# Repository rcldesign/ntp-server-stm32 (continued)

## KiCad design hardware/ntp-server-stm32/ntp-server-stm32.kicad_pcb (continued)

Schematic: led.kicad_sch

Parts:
C168: 10uF; C_1206_3216Metric; TOLERANCE 10%; VOLTAGE 16V; MANUFACTURER_PART_NUMBER CL31B106KOHVPNE; DIGIKEY_PART_NUMBER 1276-6797-1-ND
C169, C185: 0.1uF; C_0402_1005Metric; TOLERANCE 10%; VOLTAGE 16V; MANUFACTURER_PART_NUMBER GCM155R71C104KA55D; DIGIKEY_PART_NUMBER 490-4759-1-ND
C200: 1nF; C_0402_1005Metric; TOLERANCE 5%; VOLTAGE 50V; MANUFACTURER_PART_NUMBER C0402C102J5GECAUTO; DIGIKEY_PART_NUMBER 399-C0402C102J5GECAUTOCT-ND
D5: IN-P55TATRGB; LED_IN-P55TATRGB; MANUFACTURER_PART_NUMBER IN-P55TATRGB; DIGIKEY_PART_NUMBER 1830-1098-1-ND
FB12: 600; 1206; MANUFACTURER_PART_NUMBER BLM31PG601SN1L; DIGIKEY_PART_NUMBER 490-16533-1-ND
Q8, Q9, Q10, Q23: BC847W; SOT-323_SC-70; MANUFACTURER_PART_NUMBER BC847W,135; DIGIKEY_PART_NUMBER 1727-BC847W,135CT-ND
Q22: NSS40300MZ4T1G; SOT-223; MANUFACTURER_PART_NUMBER NSS40300MZ4T1G; DIGIKEY_PART_NUMBER NSS40300MZ4T1GOSCT-ND
R55: 1k; R_0402_1005Metric; TOLERANCE 1%; MANUFACTURER_PART_NUMBER ERJ-2RKF1001X; DIGIKEY_PART_NUMBER P1.00KLCT-ND
R56, R58, R63, R198, R201, R235: 10k; R_0402_1005Metric; TOLERANCE 1%; MANUFACTURER_PART_NUMBER ERJ-2RKF1002X; DIGIKEY_PART_NUMBER P10.0KLCT-ND
R57: 1.5k; R_0402_1005Metric; TOLERANCE 1%; MANUFACTURER_PART_NUMBER ERJ-2RKF1501X; DIGIKEY_PART_NUMBER P1.50KLCT-ND
R59: 60.4; R_0402_1005Metric; TOLERANCE 1%; MANUFACTURER_PART_NUMBER RK73H1ETTP60R4F; DIGIKEY_PART_NUMBER 2019-RK73H1ETTP60R4FCT-ND
R60: 174; R_0402_1005Metric; TOLERANCE 1%; MANUFACTURER_PART_NUMBER ERJ-2RKF1740X; DIGIKEY_PART_NUMBER P174LCT-ND
R61: 221; R_0402_1005Metric; TOLERANCE 1%; MANUFACTURER_PART_NUMBER RK73H1ETTP2210F; DIGIKEY_PART_NUMBER 2019-RK73H1ETTP2210FCT-ND
R62: 3.01k; R_0402_1005Metric; TOLERANCE 1%; MANUFACTURER_PART_NUMBER RK73H1ETTP3011F; DIGIKEY_PART_NUMBER 2019-RK73H1ETTP3011FCT-ND
R199: 150m; R_1206_3216Metric; TOLERANCE 0.5%; MANUFACTURER_PART_NUMBER WSL1206R1500FEA; DIGIKEY_PART_NUMBER WSLC-.15CT-ND
R216: 4.7k; R_0805_2012Metric; TOLERANCE 1%; MANUFACTURER_PART_NUMBER ERJ-6ENF4701V; DIGIKEY_PART_NUMBER P4.70KCCT-ND
R217: 820; R_0805_2012Metric; TOLERANCE 1%; MANUFACTURER_PART_NUMBER ERJ-6ENF8200V; DIGIKEY_PART_NUMBER P820CCT-ND
R234: 4.7k; R_0402_1005Metric; TOLERANCE 1%; MANUFACTURER_PART_NUMBER ERJ-2RKF4701X; DIGIKEY_PART_NUMBER P4.70KLCT-ND
R247, R248, R249, R250, R251, R252: 91; R_0805_2012Metric; TOLERANCE 1%; MANUFACTURER_PART_NUMBER ERJ-6ENF91R0V; DIGIKEY_PART_NUMBER P91.0CCT-ND
R253: 150; R_0805_2012Metric; TOLERANCE 1%; MANUFACTURER_PART_NUMBER ERJ-6ENF1500V; DIGIKEY_PART_NUMBER P150CCT-ND
U54: INA228AQDGSRQ1; VSSOP10_DGS_TEX; MANUFACTURER_PART_NUMBER INA228AQDGSRQ1; DIGIKEY_PART_NUMBER 296-INA228AQDGSRQ1CT-ND
U55: RT9742VGJ5; TSOT-23-5; MANUFACTURER_PART_NUMBER RT9742VGJ5; DIGIKEY_PART_NUMBER 1028-RT9742VGJ5TR-ND

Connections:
3V3: C169.1, U54.6 (VS); also elsewhere on the board
3V3_STM: R201.1; also elsewhere on the board
5V: R59.1, R60.1, R61.1, U55.5 (IN); also elsewhere on the board
GND: C168.2, C169.2, C185.2, C200.2, Q8.2 (E), Q9.2 (E), Q10.2 (E), Q23.2 (E), R56.2, R58.2, R63.2, R198.2, R235.2, R247.2, R248.2, R249.2, R250.2, R251.2, R252.2, R253.2, U54.2 (A0), U54.7 (GND), U55.2 (GND); also elsewhere on the board
I2C_SCL: U54.1 (A1), U54.5 (SCL); also elsewhere on the board
I2C_SDA: U54.4 (SDA); also elsewhere on the board
INA_ALERT_5V_PANEL: U54.3 (ALERT); also elsewhere on the board
LED_B: R55.2; also elsewhere on the board
LED_G: R62.2; also elsewhere on the board
LED_R: R57.2; also elsewhere on the board
unnamed: D5.6 (AB), R59.2
unnamed: D5.4 (AG), R61.2
unnamed: D5.5 (AR), R60.2
unnamed: D5.1 (KB), Q8.3 (C)
unnamed: D5.3 (KG), Q10.3 (C)
unnamed: D5.2 (KR), Q9.3 (C)
unnamed: Q8.1 (B), R55.1, R56.1
unnamed: Q9.1 (B), R57.1, R58.1
unnamed: Q10.1 (B), R62.1, R63.1
unnamed: Q22.1 (B), R217.2, R234.2
unnamed: Q23.1 (B), R216.2, R235.1
unnamed: Q23.3 (C), R217.1
unnamed: C168.1, R199.1, U54.10 (IN+), U55.1 (OUT)
unnamed: FB12.2, R199.2, U54.8 (VBUS), U54.9 (IN-)
PANEL_LEDS_P: Q22.2 (C); also elsewhere on the board
PANEL_LED_EN: R198.1, U55.4 (EN); also elsewhere on the board
PANEL_LED_FAULT: R201.2, U55.3 (nFLG); also elsewhere on the board
PANEL_LED_PWM: R216.1; also elsewhere on the board
PANEL_LED_RED_N_1: R253.1; also elsewhere on the board
PANEL_LED_WHITE_N_1: R247.1; also elsewhere on the board
PANEL_LED_WHITE_N_2: R248.1; also elsewhere on the board
PANEL_LED_WHITE_N_3: R249.1; also elsewhere on the board
PANEL_LED_WHITE_N_4: R250.1; also elsewhere on the board
PANEL_LED_WHITE_N_5: R251.1; also elsewhere on the board
PANEL_LED_WHITE_N_6: R252.1; also elsewhere on the board
V_PANEL_LED: C185.1, C200.1, FB12.1, Q22.3 (E), R234.1

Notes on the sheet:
I2C Address: 0x4C

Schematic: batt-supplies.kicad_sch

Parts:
C88, C89: 10uF; C_1206_3216Metric; TOLERANCE 10%; VOLTAGE 16V; MANUFACTURER_PART_NUMBER CL31B106KOHVPNE; DIGIKEY_PART_NUMBER 1276-6797-1-ND
C90, C91: 3F; DSF305Q3R0; TOLERANCE 5%; VOLTAGE 3V; MANUFACTURER_PART_NUMBER DSF305Q3R0; DIGIKEY_PART_NUMBER 338-DSF305Q3R0-ND
C92, C93, C94, C95, C96, C97: 22uF; C_0805_2012Metric; TOLERANCE 10%; VOLTAGE 16V; MANUFACTURER_PART_NUMBER GRT21BR61C226ME13K; DIGIKEY_PART_NUMBER 490-GRT21BR61C226ME13KCT-ND
C189: 0.1uF; C_0402_1005Metric; TOLERANCE 10%; VOLTAGE 16V; MANUFACTURER_PART_NUMBER GCM155R71C104KA55D; DIGIKEY_PART_NUMBER 490-4759-1-ND
C190, C192: 10nF; C_0402_1005Metric; TOLERANCE 10%; VOLTAGE 50V; MANUFACTURER_PART_NUMBER GCM155R71H103KA55D; DIGIKEY_PART_NUMBER 490-4762-1-ND
C191: 1uF; C_0603_1608Metric; TOLERANCE 10%; VOLTAGE 16V; MANUFACTURER_PART_NUMBER C0603C105K4RACAUTO; DIGIKEY_PART_NUMBER 399-17704-1-ND
FB11: 600; 1206; MANUFACTURER_PART_NUMBER BLM31PG601SN1L; DIGIKEY_PART_NUMBER 490-16533-1-ND
L4, L5: 2.2uH; DR73-2R2-R; MANUFACTURER_PART_NUMBER DR73-2R2-R; DIGIKEY_PART_NUMBER 283-DR73-2R2-RTR-ND
R108, R109, R110, R111, R237, R244: 100k; R_0402_1005Metric; TOLERANCE 1%; MANUFACTURER_PART_NUMBER ERJ-2RKF1003X; DIGIKEY_PART_NUMBER P100KLCT-ND
R112, R113: 13.0k; R_0402_1005Metric; TOLERANCE 1%; MANUFACTURER_PART_NUMBER ERJ-2RKF1302X; DIGIKEY_PART_NUMBER P13.0KLCT-ND
R114, R115: 9.53k; R_0402_1005Metric; TOLERANCE 1%; MANUFACTURER_PART_NUMBER ERJ-2RKF9531X; DIGIKEY_PART_NUMBER P9.53KLCT-ND
R116, R117: 3.09k; R_0402_1005Metric; TOLERANCE 1%; MANUFACTURER_PART_NUMBER ERJ-2RKF3091X; DIGIKEY_PART_NUMBER P3.09KLCT-ND
R238, R245: 2M; R_0402_1005Metric; TOLERANCE 1%; MANUFACTURER_PART_NUMBER ERJ-U02F2004X; DIGIKEY_PART_NUMBER 10-ERJ-U02F2004XCT-ND
R239, R242: 110k; R_0402_1005Metric; TOLERANCE 1%; MANUFACTURER_PART_NUMBER ERJ-2RKF1103X; DIGIKEY_PART_NUMBER P110KLCT-ND
R240, R243: 150k; R_0402_1005Metric; TOLERANCE 1%; MANUFACTURER_PART_NUMBER ERJ-2RKF1503X; DIGIKEY_PART_NUMBER P150KLCT-ND
R241, R246: 10k; R_0402_1005Metric; TOLERANCE 1%; MANUFACTURER_PART_NUMBER ERJ-2RKF1002X; DIGIKEY_PART_NUMBER P10.0KLCT-ND
U34, U35: TPS61094DSSR; SON50P300X200X80-13N; MANUFACTURER_PART_NUMBER TPS61094DSSR; DIGIKEY_PART_NUMBER 296-TPS61094DSSRCT-ND
U67: LMV393; MANUFACTURER_PART_NUMBER LMV393IDGKR; DIGIKEY_PART_NUMBER 296-13993-1-ND

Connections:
3V3: C88.1, C89.1, U34.4 (VIN), U35.4 (VIN); also elsewhere on the board
3V3_STM: R239.1, R241.1, R242.1, R246.1; also elsewhere on the board
5V: FB11.2; also elsewhere on the board
BKP_GPS_PG: R238.2, R241.2, U67.1; also elsewhere on the board
BKP_STM_PG: R245.2, R246.2, U67.7; also elsewhere on the board
GND: C88.2, C89.2, C90.2, C91.2, C92.2, C93.2, C94.2, C95.2, C96.2, C97.2, C189.2, C190.2, C191.2, C192.2, R112.2, R113.2, R114.2, R115.2, R116.2, R117.2, R240.2, R243.2, U34.7 (PGND), U34.8 (AGND), U34.13 (EXP), U35.7 (PGND), U35.8 (AGND), U35.13 (EXP), U67.4 (V-); also elsewhere on the board
GPS_VBAT: C92.1, C94.1, C96.1, R108.1, R110.1, U34.9 (VOUT), U34.10 (VOUT__1); also elsewhere on the board
unnamed: R108.2, U34.3 (EN)
unnamed: R114.1, U34.11 (ICHG)
unnamed: R110.2, U34.2 (MODE)
unnamed: R116.1, U34.1 (OSEL)
unnamed: C90.1, L4.2, R237.1, U34.6 (SUP)
unnamed: L4.1, U34.5 (SW)
unnamed: R112.1, U34.12 (VCHG)
unnamed: R109.2, U35.3 (EN)
unnamed: R115.1, U35.11 (ICHG)
unnamed: R111.2, U35.2 (MODE)
unnamed: R117.1, U35.1 (OSEL)
unnamed: C91.1, L5.2, R244.1, U35.6 (SUP)
unnamed: L5.1, U35.5 (SW)
unnamed: R113.1, U35.12 (VCHG)
unnamed: C190.1, R237.2, R238.1, U67.3 (+)
unnamed: R239.2, R240.1, U67.2 (-)
unnamed: C192.1, R244.2, R245.1, U67.5 (+)
unnamed: R242.2, R243.1, U67.6 (-)
unnamed: C189.1, C191.1, FB11.1, U67.8 (V+)
STM_VBAT: C93.1, C95.1, C97.1, R109.1, R111.1, U35.9 (VOUT), U35.10 (VOUT__1); also elsewhere on the board

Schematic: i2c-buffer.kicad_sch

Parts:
C170: 0.1uF; C_0402_1005Metric; TOLERANCE 10%; VOLTAGE 16V; MANUFACTURER_PART_NUMBER GCM155R71C104KA55D; DIGIKEY_PART_NUMBER 490-4759-1-ND
R202, R203: 4.7k; R_0402_1005Metric; TOLERANCE 1%; MANUFACTURER_PART_NUMBER ERJ-2RKF4701X; DIGIKEY_PART_NUMBER P4.70KLCT-ND
U56: LTC4311ISC6-TRPBF; SOT-6_SC_LIT; MANUFACTURER_PART_NUMBER LTC4311ISC6#TRPBF; DIGIKEY_PART_NUMBER LTC4311ISC6#TRPBFCT-ND

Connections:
3V3_STM: C170.1, R202.1, R203.1, U56.1 (VCC), U56.3 (ENABLE); also elsewhere on the board
GND: C170.2, U56.2 (GND), U56.5 (GND); also elsewhere on the board
I2C_SCL: R202.2, U56.6 (BUS1); also elsewhere on the board
I2C_SDA: R203.2, U56.4 (BUS2); also elsewhere on the board

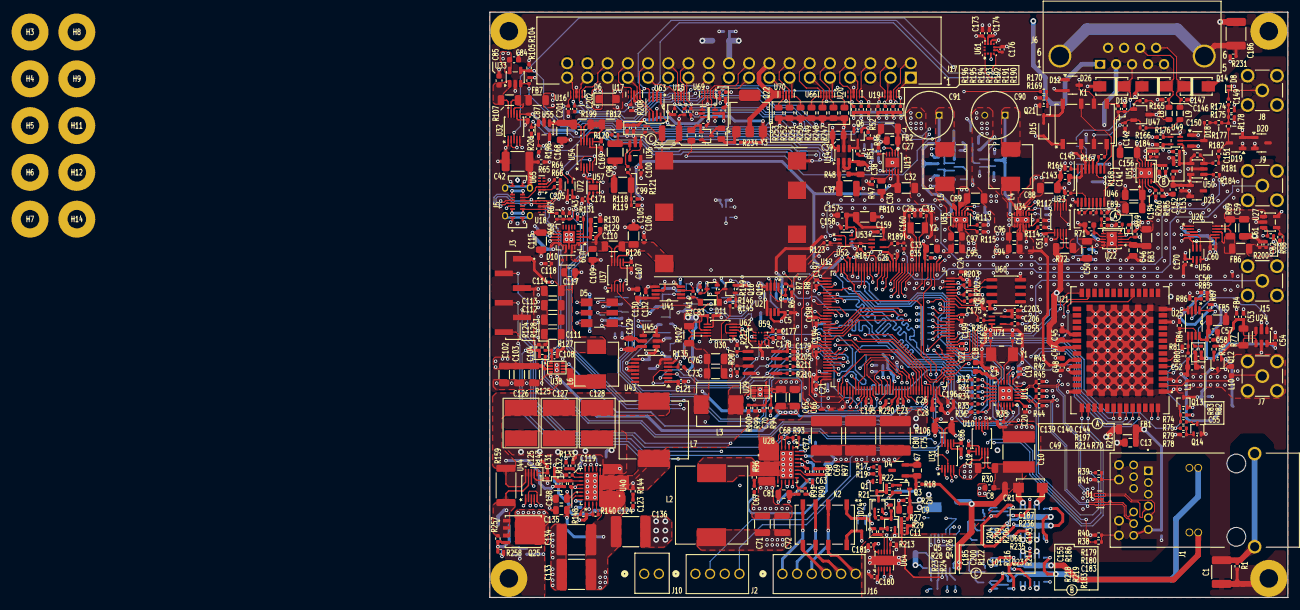
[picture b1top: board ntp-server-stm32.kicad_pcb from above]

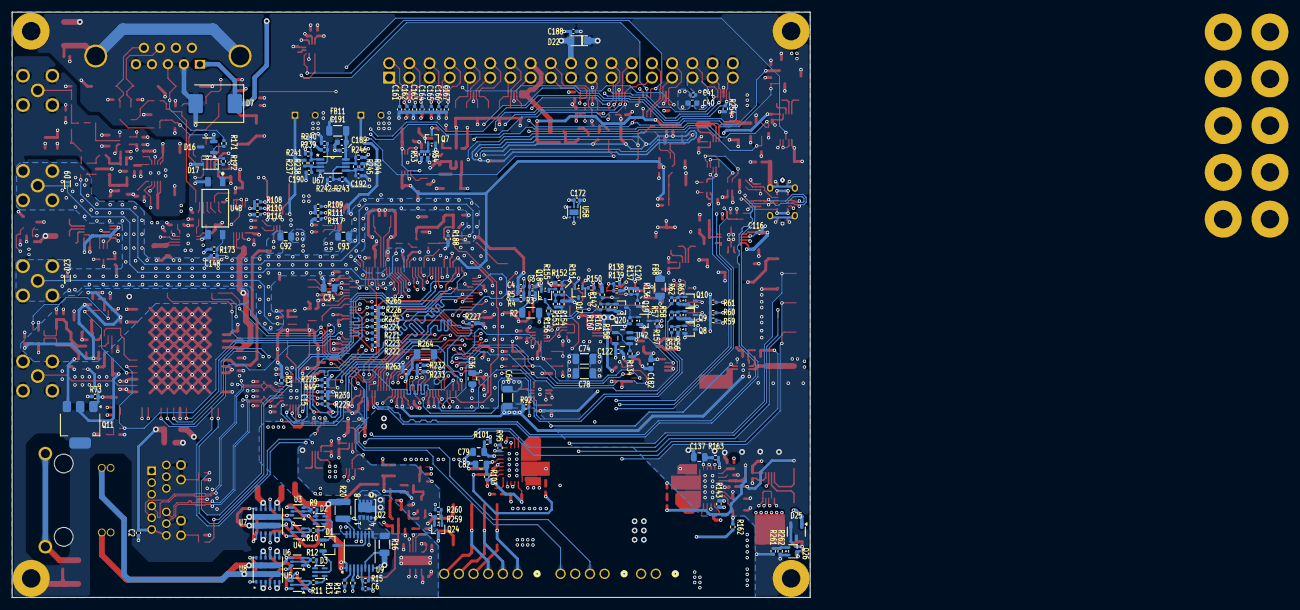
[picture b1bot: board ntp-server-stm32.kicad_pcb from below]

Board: 6 copper layers, 138.2 x 101.3 mm, 648 parts (161 on the bottom side), 387 nets.

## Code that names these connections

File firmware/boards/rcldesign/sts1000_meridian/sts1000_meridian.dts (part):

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 *
 * MCU: STM32H563ZIT6, LQFP144.  There are NO spare GPIO on this package; PE1
 * and PB11 are not bonded (their die pads carry VCAP1/VCAP2), and PH1/OSC_OUT
 * (pin 24) is the single uncommitted pin because PH0 runs in HSE-bypass.
 *
 * Pin↔net authority: docs/sts1000_firmware_hardware_interface.md §1 (the
 * as-built 144-pin contract).  Net names below match the canonical names in
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
	aliases {
		/*
		 * MCUboot serial-recovery entry button: BUTTON_1 (PF0), held
		 * low at reset.  See sysbuild/mcuboot.conf.
		 */
		mcuboot-button0 = &button_1;
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		status = "disabled";

		button_1: button_1 {
			label = "BUTTON_1";
			gpios = <&gpiof 0 GPIO_ACTIVE_LOW>;
			zephyr,code = <INPUT_KEY_1>;
		};

		button_2: button_2 {
			label = "BUTTON_2";
			gpios = <&gpiof 1 GPIO_ACTIVE_LOW>;
			zephyr,code = <INPUT_KEY_2>;
		};

		button_3: button_3 {
			label = "BUTTON_3";
			gpios = <&gpiof 2 GPIO_ACTIVE_LOW>;
			zephyr,code = <INPUT_KEY_3>;
		};

		button_4: button_4 {
			label = "BUTTON_4";
			gpios = <&gpiof 3 GPIO_ACTIVE_LOW>;
			zephyr,code = <INPUT_KEY_4>;
		};

		button_5: button_5 {
			label = "BUTTON_5";
			gpios = <&gpiof 4 GPIO_ACTIVE_LOW>;
			zephyr,code = <INPUT_KEY_5>;
		};

		button_6: button_6 {
			label = "BUTTON_6";
			gpios = <&gpiof 5 GPIO_ACTIVE_LOW>;
			zephyr,code = <INPUT_KEY_6>;
		};

		button_7: button_7 {
			label = "BUTTON_7";
			gpios = <&gpiof 6 GPIO_ACTIVE_LOW>;
			zephyr,code = <INPUT_KEY_7>;
		};

		encoder_button: encoder_button {
			label = "ENC_BUTTON";
			gpios = <&gpiof 11 GPIO_ACTIVE_LOW>;
			zephyr,code = <INPUT_KEY_ENTER>;
		};
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	 * mean "asserted" for every one of them.
	 *
	 * Not listed here (owned elsewhere in this DTS): SPI4 chip-selects
	 * PE11/PD2/PE9 (&spi4 cs-gpios), the keypad (gpio_keys), and every
	 * pin claimed by a pinctrl group.
	 */
	zephyr_user: zephyr,user {
		/* ---- Stage 2: release held-in-reset digital devices ---- */
		/* PE10 NOR_RST_N — boots asserted via R205 10k pull-down. */
		nor-rst-gpios = <&gpioe 10 GPIO_ACTIVE_LOW>;
		/* PA10 DISP_RST — boots asserted via R209 10k pull-down. */
		disp-rst-gpios = <&gpioa 10 GPIO_ACTIVE_LOW>;

		/* ---- Stage 4: PHY ---- */
		/* PD10 LAN_RST_N — boots asserted via R35 10k pull-down. */
		lan-rst-gpios = <&gpiod 10 GPIO_ACTIVE_LOW>;

		/* ---- Stage 5: GNSS + antenna ---- */
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		gps-dsel-gpios = <&gpiod 7 GPIO_ACTIVE_HIGH>;
		gps-extint-gpios = <&gpiod 6 GPIO_ACTIVE_HIGH>;
		ant-bias-en-gpios = <&gpioc 9 GPIO_ACTIVE_HIGH>;
		/* PD4 GPS_ANT_OFF_MON: high = F9T has disabled the LNA. */
		gps-ant-off-gpios = <&gpiod 4 GPIO_ACTIVE_HIGH>;
		/*
		 * PD5 GPS_TXRDY: F9T pin 19 defaults to GEOFENCE_STAT — trust
		 * this only after the CFG-TXREADY remap is ACKed
		 * (ARCHITECTURE §10.8).
		 */
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
		/* ---- Stage 6: display / panel (deferrable) ---- */
		disp-en-gpios = <&gpioc 11 GPIO_ACTIVE_HIGH>;
		/* PB0 DISP_DC: high = data, low = command. */
		disp-dc-gpios = <&gpiob 0 GPIO_ACTIVE_HIGH>;
		disp-touch-int-gpios = <&gpiof 7 GPIO_ACTIVE_LOW>;
		panel-led-en-gpios = <&gpioc 0 GPIO_ACTIVE_HIGH>;
		/*
		 * PE0 PANEL_LED_PWM. No timer output channel reaches PE0 on
		 * STM32H563 (AF table has TIM4_ETR only), so this is a plain
		 * GPIO for now — see the TODO in prj.conf.
		 */
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
		/* ---- Timing reference selection ---- */
		/*
		 * PB6 MUX_SEL — 0 = OCXO (boot default via R188 100k
		 * pull-down), 1 = Rb.  Written ONLY by the refsel action
		 * executor, always inside the HSI-bridge sequence
		 * (ARCHITECTURE §10.1).
		 */
		mux-sel-gpios = <&gpiob 6 GPIO_ACTIVE_HIGH>;
		/* PC10 REF_TERM_EN — boots terminated (R176 100k pull-up). */
		ref-term-en-gpios = <&gpioc 10 GPIO_ACTIVE_HIGH>;

		/* ---- Stage 8: rubidium (guarded) ---- */
		rb-pwr-en-gpios = <&gpiob 7 GPIO_ACTIVE_HIGH>;
		rb-vcc-gate-gpios = <&gpiob 1 GPIO_ACTIVE_HIGH>;
		/* PD3 RB_OV_RESET — pulse high to clear the 26 V OV latch. */
		rb-ov-reset-gpios = <&gpiod 3 GPIO_ACTIVE_HIGH>;
		/* PE3 RB_OV_DET — high = OV latch tripped.  Polled. */
		rb-ov-det-gpios = <&gpioe 3 GPIO_ACTIVE_HIGH>;
		/* PE4 — de-energized relay = RS-232 (fail-safe); high = CMOS. */
		rb-rs232-cmos-gpios = <&gpioe 4 GPIO_ACTIVE_HIGH>;
		/*
		 * PB13 RB_LOCK — opto U48 inverts, so the electrical sense is
		 * a firmware config bit.  DT carries the raw (uninverted) pin
		 * polarity; `refsel` applies the configured inversion.
		 */
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		/* ---- Stage 9: watchdog, alarms, kill ---- */
		wdt-kick-gpios = <&gpiob 2 GPIO_ACTIVE_HIGH>;
		wdt-en-gpios = <&gpioc 12 GPIO_ACTIVE_HIGH>;
		/* PE15 POE_KILL — low = RUN; high latches a board cold-cycle. */
		poe-kill-gpios = <&gpioe 15 GPIO_ACTIVE_HIGH>;
		/*
		 * PA6 K2 holdover relay — normally-ENERGIZED fail-safe.  HIGH
		 * only once service quality is met (ARCHITECTURE §10.6).
		 */
		holdover-relay-gpios = <&gpioa 6 GPIO_ACTIVE_HIGH>;

		/* ---- Power / supervisory inputs ---- */
		/* PE8 PFI — falling edge = imminent power fail (EXTI8). */
		pfi-gpios = <&gpioe 8 GPIO_ACTIVE_LOW>;
		/* PA15 FAN_TACH — no external pull; use the internal one. */
		fan-tach-gpios = <&gpioa 15 (GPIO_ACTIVE_HIGH | GPIO_PULL_UP)>;
		/*
		 * PE2 USB_VBUS_SENSE.  The as-built net is a divider
		 * (k ~= 0.547, ~2.87 V at VBUS 5.25 V) intended for an ADC, but
		 * STM32H563 has no ADC channel on PE2 (ADC1/2 inputs are
		 * PA0-PA7, PB0/PB1, PC0-PC5, PF11-PF14 only).  Read it as a
		 * digital level instead: 2.87 V is comfortably above VIH.
		 * Polled, never EXTI — EXTI2 belongs to PC2 (interface ref §6).
		 */
		usb-vbus-sense-gpios = <&gpioe 2 GPIO_ACTIVE_HIGH>;
		/*
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
		/*
		 * ---- Rail power-good, GPIOG bits 0..7 (interface ref §5.2) --
		 * Active-high "good".  All eight are usable; PG2 no longer
		 * needs masking now that R266 is fitted.
		 */
		pg-3v3-gps-gpios = <&gpiog 0 GPIO_ACTIVE_HIGH>;
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
		/*
		 * ---- INA228 ALERT lines (open-drain, active-low) ----
		 * Eight on GPIOG 8..15, plus the panel monitor on PF13.
		 * Addresses per interface ref §4: GPS is 0x4A (SHT45 owns
		 * 0x44) and the panel monitor is 0x4C.
		 */
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		ina-alert-5v-panel-gpios = <&gpiof 13 GPIO_ACTIVE_LOW>;	/* 0x4C */

		/* ---- Analog / bus handles for later waves ---- */
		/* OCXO Vc read-back (PA3, ADC1_INP15). */
		io-channels = <&adc1 15>;
		/* OCXO steering (PA4, DAC1_OUT1); centre code = 1.65 V. */
		dac = <&dac1>;
		dac-channel-id = <1>;
		dac-resolution = <12>;
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 * ---------------------------------------------------------------------------
 * Clock tree
 * ---------------------------------------------------------------------------
 * PH0 is an HSE *bypass* input fed by the 74LVC1G157 clock mux (U52), i.e. the
 * disciplined 10 MHz from either the OH300 OCXO or the FE-5680A rubidium.  Both
 * references are 10 MHz, so a single PLL configuration serves both and the
 * OCXO<->Rb handoff never needs a PLL re-programme (interface ref §3).
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	status = "okay";
};

/* 32.768 kHz crystal on PC14/PC15 — RTC / backup domain time base. */
&clk_lse {
	status = "okay";
};
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/* ---------------------------------------------------------------------------
 * Networking — LAN8742AI RMII PHY, MAC IEEE-1588 hardware timestamping.
 * The PHY runs in REFCLKO mode (nINTSEL = 0) and sources the 50 MHz RMII
 * reference clock into PA1.  There is no PHY interrupt line: link state comes
 * from MDIO polling.  PB10/RMII_RXER and PA7/RMII_CRS_DV double as PHY straps
 * (PHYAD0 / MODE2) on the PHY side, so they must stay Hi-Z through PHY reset —
 * this is why LAN_RST_N is released explicitly in Stage 4 rather than at boot.
 * ---------------------------------------------------------------------------
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		     &eth_txd1_pb15
		     &eth_rxd0_pc4
		     &eth_rxd1_pc5
		     /* PB5 ETH_PPS_OUT — MAC 1588 PPS -> U71 buffer -> J15. */
		     &eth_pps_out_pb5>;
	pinctrl-names = "default";
	phy-connection-type = "rmii";
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};

/* ---------------------------------------------------------------------------
 * I²C1 (PB8/PB9) — 15-device 400 kHz housekeeping bus, all on always-on
 * 3V3_STM.  Only devices with in-tree drivers are instantiated here; the nine
 * INA228 monitors and the ATECC608B are driven as raw I²C from application
 * code (core/ina228 + CryptoAuthLib), so they deliberately have no DT nodes.
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};

/* ---------------------------------------------------------------------------
 * SPI4 (PE12 SCK / PE13 MISO / PE14 MOSI) — three devices, distinct CS.
 * Firmware must arbitrate with a bus mutex and reconfigure CPOL/CPHA/speed per
 * device (interface ref §9).
 *   cs-gpios[0] PE11  SPI_NSS      -> NOR U62      (MX25L25645G)
 *   cs-gpios[1] PD2   SPI_DPOT_CS  -> digipot U43  (MCP41U83, mode 0,0)
 *   cs-gpios[2] PE9   DISP_CS      -> display      (ST7796)
 * Only the NOR gets a driver node this wave: the digipot is raw SPI from
 * core/pwrseq and the display subsystem is deferred.
 * ---------------------------------------------------------------------------
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	 * stateful EN4B mode — that keeps the part addressable even if it is
	 * reset asynchronously by NOR_RST_N.
	 *
	 * NOR_RST_N (PE10) is deliberately NOT wired as `reset-gpios` here:
	 * the bring-up sequencer owns that pin (interface ref §2 Stage 2,
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
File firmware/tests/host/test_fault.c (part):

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	scan_for(&m, 3U);

	/*
	 * PF7 carries no debounce capacitor (fault-aggregation doc §4) and the
	 * INT is a request to read the controller over I2C, so the very first
	 * scan that sees it low must dispatch.
	 */
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	scan_for(&m, 3U);

	/* One scan is not enough. */
	m.g = clr(m.g, 8U); /* PG8 INA_ALERT_V_POE */
	scan_for(&m, 1U);
	TEST_ASSERT_FALSE(fault_asserted(&m.ctx, FAULT_SIG_INA_ALERT_V_POE));
	expect_empty(&m);
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	model_init(&m, &cfg);
	scan_for(&m, 2U);

	m.g = clr(m.g, 15U); /* PG15 INA_ALERT_VCC_RB */
	scan_for(&m, 3U);
	TEST_ASSERT_FALSE(fault_asserted(&m.ctx, FAULT_SIG_INA_ALERT_VCC_RB));
	scan_for(&m, 1U);
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	model_init(&m, NULL);
	scan_for(&m, 1U);

	/* PF11 is scanned; the quadrature A/B on PA8/PA9 is not (TIM1). */
	TEST_ASSERT_EQUAL_INT(FAULT_CLASS_BUTTON,
			      fault_sig_class(FAULT_SIG_ENC_BUTTON));

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	model_init(&m, NULL);
	scan_for(&m, 10U);

	/* PG1 OCXO_LDO_PG goes high->low: rail fault. */
	m.g = clr(m.g, 1U);
	scan_for(&m, 6U);
	expect_evt(&m, FAULT_EVT_PG_FAULT, FAULT_SIG_PG_OCXO_LDO,
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
	/*
	 * Interface ref §5.2: "All eight PG bits are usable — no masking."
	 * PG2 (3V0_RF_LDO_PG) used to need masking; R266 is now fitted, so a
	 * regression that special-cased it would show up here.
	 */
	for (b = 0U; b < 8U; b++) {
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	model_init(&m, NULL);
	scan_for(&m, 2U);

	/* Eight on GPIOG[8:15] plus the panel monitor on PF13. */
	for (b = 8U; b < 16U; b++) {
		m.g = clr(m.g, b);
	}
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	TEST_ASSERT_TRUE(fault_asserted(&m.ctx, FAULT_SIG_INA_ALERT_PANEL));
	TEST_ASSERT_TRUE(fault_asserted(&m.ctx, FAULT_SIG_INA_ALERT_VCC_RB));

	/* The panel alert dispatches first because PF13 precedes GPIOG in the
	 * combined bitmap — identity is preserved either way. */
	expect_evt(&m, FAULT_EVT_INA_ALERT, FAULT_SIG_INA_ALERT_PANEL,
		   FAULT_EDGE_ASSERT);
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
	/*
	 * MEDIUM-1: a deferred or shed rubidium is a first-class non-fault
	 * outcome, but its buck power-good (PG6 RB_PSU) reads low forever after.
	 * Without the expected-off mask that alarm sits active and holds
	 * fault_any_active() true — a healthy OCXO-only unit glowing red. pwrseq
	 * marks the rail expected-off as it declines to power it.
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				 fault_expected_off_mask(&m.ctx));

	/* The rail drops. The level and the event are still real... */
	m.g = clr(m.g, 6U); /* PG6 RB_PSU_PG */
	scan_for(&m, 6U);
	expect_evt(&m, FAULT_EVT_PG_FAULT, FAULT_SIG_PG_RB_PSU,
		   FAULT_EDGE_ASSERT);
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
	/* A scanned fault and its alarm are the same id, so a consumer can go
	 * straight from an event to the latch entry. */
	m.g = clr(m.g, 7U); /* PG7 POE_PG */
	scan_for(&m, 6U);

	TEST_ASSERT_TRUE((fault_alarms(&m.ctx) &
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
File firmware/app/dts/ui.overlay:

/*
 * STS1000 "Meridian" — local-UI devicetree overlay.
 *
 * SPDX-License-Identifier: Apache-2.0
 *
 * Merged after the board .dts by app/CMakeLists.txt. Adds only the display
 * subsystem; every other pin the UI area touches (DISP_EN/PC11, DISP_RST/PA10,
 * DISP_DC/PB0, PROX_WAKE, the touch INT) is already declared in the board's
 * /zephyr,user node, and the encoder and backlight ride nodes the board
 * already defines (`panel_qdec` on TIM1, `panel_pwm` on TIM15).
 *
 * ---------------------------------------------------------------------------
 * Why the in-tree ST7796S driver, and how it shares SPI4
 * ---------------------------------------------------------------------------
 * The panel is a Sitronix ST7796S over SPI4, write-only (J17 carries
 * SPI_SCK_DISP and SPI_MOSI_DISP but no MISO — interface ref §9). Zephyr 4.2
 * ships `sitronix,st7796s` on top of the MIPI-DBI mode-C shim
 * (`zephyr,mipi-dbi-spi`), which is exactly this wiring: a SPI controller plus
 * a data/command GPIO plus a reset GPIO.
 *
 * The shared-bus question resolves in the shim's favour rather than against it.
 * MIPI_DBI_SPI_CONFIG_DT() takes the chip select from the *parent's* `spi-dev`
 * phandle at index `reg`, so `reg = <2>` below selects &spi4's cs-gpios[2] =
 * PE9 = DISP_CS, leaving cs-gpios[0] (NOR) and cs-gpios[1] (digipot)
 * untouched. Zephyr's SPI driver serialises transfers per controller and
 * re-applies each device's spi_config, so the NOR at 40 MHz mode 0, the
 * MCP41U83 at mode 0,0 and the panel at 30 MHz coexist without an application
 * mutex. A hand-rolled ST7796 driver was therefore not needed and is not used.
 *
 * ---------------------------------------------------------------------------
 * Deferred init
 * ---------------------------------------------------------------------------
 * Both nodes are `zephyr,deferred-init`. Spec §6.5 requires DISP_EN (PC11) to
 * come up first so the RT9742 soft-starts 5V_DISP and the PCA9306 enables,
 * and only then DISP_RST to be released. That ordering is owned by
 * src/zephyr/ui/ui_display.c, which asserts the rail, waits, and calls
 * device_init() on the shim and then the panel. Left to POST_KERNEL the panel
 * driver would push its whole init sequence into an unpowered module.
 *
 * `reset-gpios` on the shim (not on /zephyr,user) is deliberate: st7796s_init()
 * calls mipi_dbi_reset() unconditionally and fails with -ENOTSUP if the shim
 * has no reset pin, and the same DISP_RST line also resets the FT6336U, whose
 * initialisation the UI area runs immediately after the panel's — one owner,
 * one pulse, both devices.
 */

/ {
	disp_dbi: mipi-dbi {
		compatible = "zephyr,mipi-dbi-spi";
		spi-dev = <&spi4>;
		/* PB0 DISP_DC: high = data, low = command. */
		dc-gpios = <&gpiob 0 GPIO_ACTIVE_HIGH>;
		/* PA10 DISP_RST: active low, held asserted at boot by R209. */
		reset-gpios = <&gpioa 10 GPIO_ACTIVE_LOW>;
		write-only;
		#address-cells = <1>;
		#size-cells = <0>;
		zephyr,deferred-init;
		status = "okay";

		display: st7796s@2 {
			compatible = "sitronix,st7796s";
			/* Index into &spi4 cs-gpios: [2] = PE9 DISP_CS. */
			reg = <2>;
			mipi-max-frequency = <DT_FREQ_M(30)>;
			mipi-mode = "MIPI_DBI_MODE_SPI_4WIRE";

			/*
			 * Landscape. The panel is 320RGB x 480 native; MADCTL
			 * MV|MX exchanges the axes and mirrors the column
			 * order, giving 480 x 320 with the origin top-left for
			 * a rack-front orientation. BGR is set because the
			 * common ST7796S modules wire the panel that way.
			 *
			 * BENCH: confirm orientation and colour order against
			 * the fitted module; a mirrored image is MX (0x40) and
			 * swapped red/blue is BGR (0x08).
			 */
			width = <480>;
			height = <320>;
			madctl = <0x68>;
			invert-mode = "1-dot";

			/*
			 * Gamma: 14 bytes each into E0h/E1h. The binding
			 * requires both and offers no default because the
			 * curve is panel specific. These are the ST7796S
			 * application-note values — a neutral starting point,
			 * not a characterisation of the fitted glass.
			 *
			 * BENCH: adjust against the module's own init table
			 * once one is fitted; a wrong gamma is a washed-out or
			 * crushed image, never a functional failure.
			 */
			pgc = [F0 09 0B 06 04 15 2F 54 42 3C 17 14 18 1B];
			ngc = [E0 09 0B 06 04 03 2B 43 42 3B 16 14 17 1B];

			zephyr,deferred-init;
			status = "okay";
		};
	};
};

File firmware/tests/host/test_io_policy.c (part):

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	TEST_ASSERT_EQUAL_UINT8('G', port);
	TEST_ASSERT_EQUAL_UINT8(15U, bit);

	/* Documented pins, straight from interface ref §5: PF13 is the one INA
	 * alert on GPIOF, PG8 is the first one on GPIOG. */
	TEST_ASSERT_EQUAL_INT(
		0, sts_io_sig_port_bit(FAULT_SIG_INA_ALERT_PANEL, &port, &bit));
	TEST_ASSERT_EQUAL_UINT8('F', port);
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	uint8_t addr;
	const char *designator;
} alert_map[] = {
	{ FAULT_SIG_INA_ALERT_PANEL, 0x4CU, "U54" },   /* PF13 — panel-LED 5 V */
	{ FAULT_SIG_INA_ALERT_V_POE, 0x40U, "U10" },   /* PG8  — PoE input */
	{ FAULT_SIG_INA_ALERT_3V3_STM, 0x41U, "U31" }, /* PG9 */
	{ FAULT_SIG_INA_ALERT_5V_DISP, 0x42U, "U32" }, /* PG10 */
	{ FAULT_SIG_INA_ALERT_3V3, 0x43U, "U30" },     /* PG11 */
	{ FAULT_SIG_INA_ALERT_3V3_GPS, 0x4AU, "U23" }, /* PG12 — NOT 0x44 */
	{ FAULT_SIG_INA_ALERT_V_ANT, 0x45U, "U26" },   /* PG13 */
	{ FAULT_SIG_INA_ALERT_OCXO, 0x46U, "U37" },    /* PG14 */
	{ FAULT_SIG_INA_ALERT_VCC_RB, 0x47U, "U44" },  /* PG15 */
};

static void test_alert_signal_resolves_to_the_documented_monitor(void)
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
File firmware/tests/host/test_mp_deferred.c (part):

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 * this seam.
 *
 * `sys.wdt.kick` joined for the same reason and is the clearest case of it:
 * WDI rests low between edges, so a read of PB2 would report "not pulsing"
 * forever. What a technician actually needs to confirm before pulsing it is
 * `sys.wdt.en` — the watchdog is not watching — and that object DOES read back.
 */
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}

/**
 * THE CONSOLE NEVER WRITES PA4.
 *
 * Spec §3 makes the discipline thread the only writer of DAC1_OUT1 and the
 * owner of disc_ctx_t. `ref.disc.park`, `ref.ocxo.vc_mv` and `ref.ocxo.dac_code`
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
		(void)snprintf(msg, sizeof(msg),
			       "mp_glue.c calls `%s`; the console thread has "
			       "reached the discipline loop's actuator and PA4 "
			       "now has two writers",
			       forbidden[k]);
		TEST_ASSERT_EQUAL_UINT_MESSAGE(0U, count_in(&all, forbidden[k]),
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/**
 * ...and the discipline thread is where the actuation actually happens.
 *
 * The other half of the assertion above: proving mp_glue.c does not write PA4
 * is worth nothing if nobody else does either, which would make the objects
 * silently inert. The drain claims each row, and the Vc executor is the one
 * place disc_write_dac() is reached from a request.
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 * They were both derived from `quality_block_t::active_ref` — the reference the
 * discipline loop had SELECTED — so `extref_ok && rb_lock` demanded one field
 * hold two mutually exclusive values and `ref.mux.sel = 1` was unsatisfiable by
 * construction. The fix is that they now read RB_LOCK (PB13) and EXTREF_MON
 * (PB14/TIM12) out of the sequencer's published OBSERVED half, which is what
 * spec §3.5 names for the handoff.
 */
static void test_the_mux_guard_reads_two_hardware_signals(void)
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	b = fn_body("static int prov_ilk(void *user, mp_ilk_state_t *out)");

	TEST_ASSERT_EQUAL_UINT_MESSAGE(
		1U, count_in(&b, "out->rb_lock = ps.rb_lock_pin;"),
		"rb_lock no longer reads RB_LOCK");
	TEST_ASSERT_EQUAL_UINT_MESSAGE(
		1U, count_in(&b, "out->extref_ok = ps.extref_valid && "
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		"`sys.wdt.en` no longer actuates through the supervisor");
	TEST_ASSERT_EQUAL_UINT_MESSAGE(
		0U, count_in(&b, "gpio_pin_set_dt"),
		"obj_apply() writes a GPIO directly; WDT_EN and MUX_SEL both "
		"carry a sequence the pin alone does not express");

	/*
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		"the re-arm seeds the cadence before feeding the window");
	TEST_ASSERT_TRUE_MESSAGE(
		offset_in(&b, "pwrseq_wdt_arm(&super.wdt") <
			offset_in(&b, "gpio_pin_set_dt(&wdt_en, 1)"),
		"WDT_EN is raised before the cadence is seeded — the runaway "
		"fault sts_supervisor_arm() exists to avoid");
	/* Disabling stops the kicker as well as dropping the pin: wdt_entry()
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	 * be fighting a window pwrseq still believed was open. */
	TEST_ASSERT_TRUE_MESSAGE(
		offset_in(&b, "super.armed = false;") <
			offset_in(&b, "gpio_pin_set_dt(&wdt_en, 0)"),
		"the disable drops WDT_EN before it stops the kicker");

	b = fn_body("int sts_supervisor_wdt_kick(void)");
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/**
 * `ref.mux.sel` never becomes a pin write, and its release restores AUTO.
 *
 * PB6 selects which 10 MHz reaches PH0, the HSE bypass input SYSCLK derives
 * from. Flipping it under a live HSE feed skips the HSI bridge and glitches
 * SYSCLK (spec §3.5), so the actuation is refsel's bracketed handoff —
 * PARK_DISCIPLINE, mux flip, UNPARK — reached by posting the standing request.
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
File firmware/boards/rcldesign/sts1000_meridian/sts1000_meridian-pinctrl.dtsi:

/*
 * STS1000 "Meridian" — board pin-control overrides.
 *
 * Copyright (c) 2026 RCL Design
 * SPDX-License-Identifier: Apache-2.0
 *
 * Every pin group the board uses already exists in the SoC pin-control package
 * (`st/h5/stm32h563zitx-pinctrl.dtsi`, included by the board .dts before this
 * file).  This file only carries deltas that follow from *this board's*
 * schematic, so that the .dts can keep referencing the standard node names.
 *
 * Pin↔net authority: docs/sts1000_firmware_hardware_interface.md §1.
 */

/*
 * I²C1 (PB8 `I2C_SCL` / PB9 `I2C_SDA`) is a 15-device 400 kHz bus with
 * *external* 4.7 kΩ pull-ups to 3V3_STM (R202/R203) plus an LTC4311 rise-time
 * accelerator (U56, EN strapped high).  The SoC package enables the internal
 * pull-ups, which would sit in parallel with the designed bus impedance and
 * skew the rise-time budget the accelerator was sized against — remove them and
 * let the board resistors define the bus.  Open-drain is kept.
 */
&i2c1_scl_pb8 {
	/delete-property/ bias-pull-up;
};

&i2c1_sda_pb9 {
	/delete-property/ bias-pull-up;
};

/*
 * SPI4 is a three-device shared bus (NOR U62, digipot U43, display) whose
 * chip-selects all have external 10 kΩ pull-ups.  The SoC package biases
 * SCK/MISO/MOSI down, which is the correct idle state for SPI mode 0 and is
 * kept.  MOSI/SCK carry 22 Ω source terminators (R210/R211) toward the display;
 * hold the pin slew rate high so the series network — not the driver — shapes
 * the edge.
 */
&spi4_mosi_pe14 {
	slew-rate = "very-high-speed";
};

/*
 * PANEL_LED_PWM on PE0 is LPTIM2_CH2 (AF3).  genpinctrl.py does not emit LPTIM
 * pin groups for any STM32 family — the in-tree LPTIM driver is only ever a
 * kernel-tick source and needs no pins — so the group the platform's panel-PWM
 * glue references is declared here rather than pulled from the SoC package.
 *
 * AF3 = LPTIM2_CH2 is from the STM32H563 alternate-function table
 * (modm-devices `stm32h5-62_63_73.xml`, the source CLAUDE.md nominates when ST
 * pin data is not to hand: PE0 carries AF1 LPTIM1_ETR, AF2 TIM4_ETR, AF3
 * LPTIM2_CH2, AF4 LPTIM2_ETR, ...).  This corrects the earlier board note that
 * claimed no timer output reaches PE0.
 *
 * Open-drain would need an external pull to the LED-string gate; the Q23 base
 * network is a simple pull-down, so push-pull is correct here.
 */
&pinctrl {
	/omit-if-no-ref/ lptim2_ch2_pe0: lptim2_ch2_pe0 {
		pinmux = <STM32_PINMUX('E', 0, AF3)>;
	};
};

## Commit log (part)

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2026-06-21 initial schematic
